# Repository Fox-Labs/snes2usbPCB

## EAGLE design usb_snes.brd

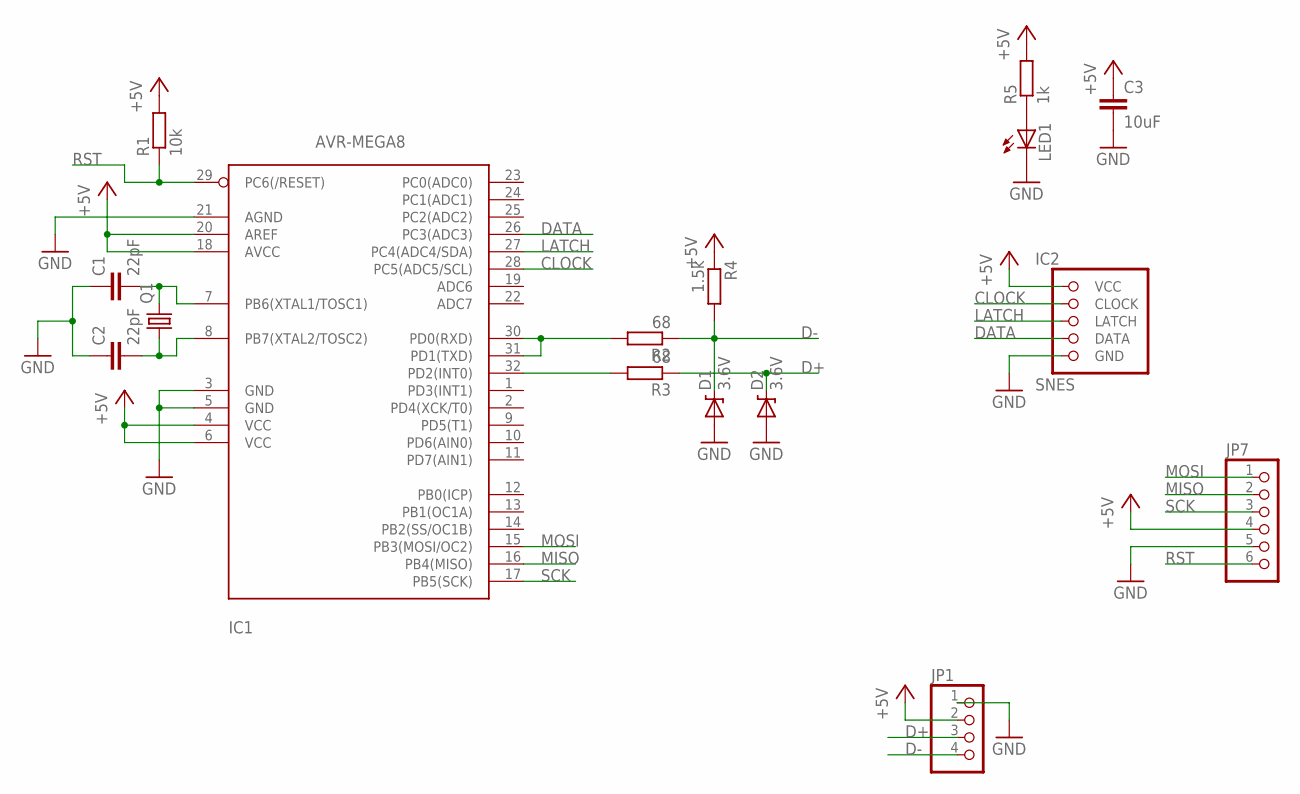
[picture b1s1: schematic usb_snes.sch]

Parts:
C1, C2: 22pF; R0805
C3: 10uF; R0805
D1, D2: 3.6V; SOD123FL
IC1: AVR-MEGA8; TQFP32-08
IC2: SNES
JP1: PINHD-1X4S; 1X04-2MM
JP7: PINHD-1X6S; 1X06-2MM
LED1: LED0805; CHIP-LED0805
Q1: CRYSTALHC49UP; HC49UP
R1: 10k; R0805
R2, R3: 68; R0805
R4: 1.5k; R0805
R5: 1k; R0805

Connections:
+5V: C3.1, IC1.4 (VCC), IC1.6 (VCC), IC1.18 (AVCC), IC1.20 (AREF), IC2.5 (VCC), JP1.2, JP7.4, R1.2, R4.1, R5.2
CLOCK: IC1.28 (PC5(ADC5/SCL)), IC2.4 (CLOCK)
D+: D2.C, JP1.3, R3.1
D-: D1.C, JP1.4, R2.1, R4.2
DATA: IC1.26 (PC3(ADC3)), IC2.2 (DATA)
GND: C1.1, C2.1, C3.2, D1.A, D2.A, IC1.3 (GND), IC1.5 (GND), IC1.21 (AGND), IC2.1 (GND), JP1.1, JP7.5, LED1.C
LATCH: IC1.27 (PC4(ADC4/SDA)), IC2.3 (LATCH)
MISO: IC1.16 (PB4(MISO)), JP7.2
MOSI: IC1.15 (PB3(MOSI/OC2)), JP7.1
unnamed: C2.2, IC1.8 (PB7(XTAL2/TOSC2)), Q1.1
unnamed: C1.2, IC1.7 (PB6(XTAL1/TOSC1)), Q1.2
unnamed: IC1.30 (PD0(RXD)), IC1.31 (PD1(TXD)), R2.2
unnamed: IC1.32 (PD2(INT0)), R3.2
unnamed: LED1.A, R5.1
RST: IC1.29 (PC6(/RESET)), JP7.6, R1.1
SCK: IC1.17 (PB5(SCK)), JP7.3

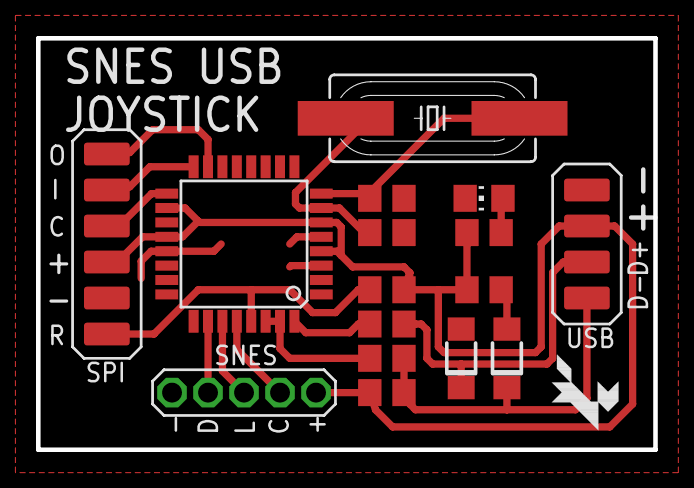
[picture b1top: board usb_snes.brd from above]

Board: 2 copper layers, 34.3 x 22.9 mm, 17 parts (0 on the bottom side), 16 nets.

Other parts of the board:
U$1: FOX-1

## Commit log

2017-06-01 - Initial version of the PCB
2017-06-01 - Second and better version of the PCB
